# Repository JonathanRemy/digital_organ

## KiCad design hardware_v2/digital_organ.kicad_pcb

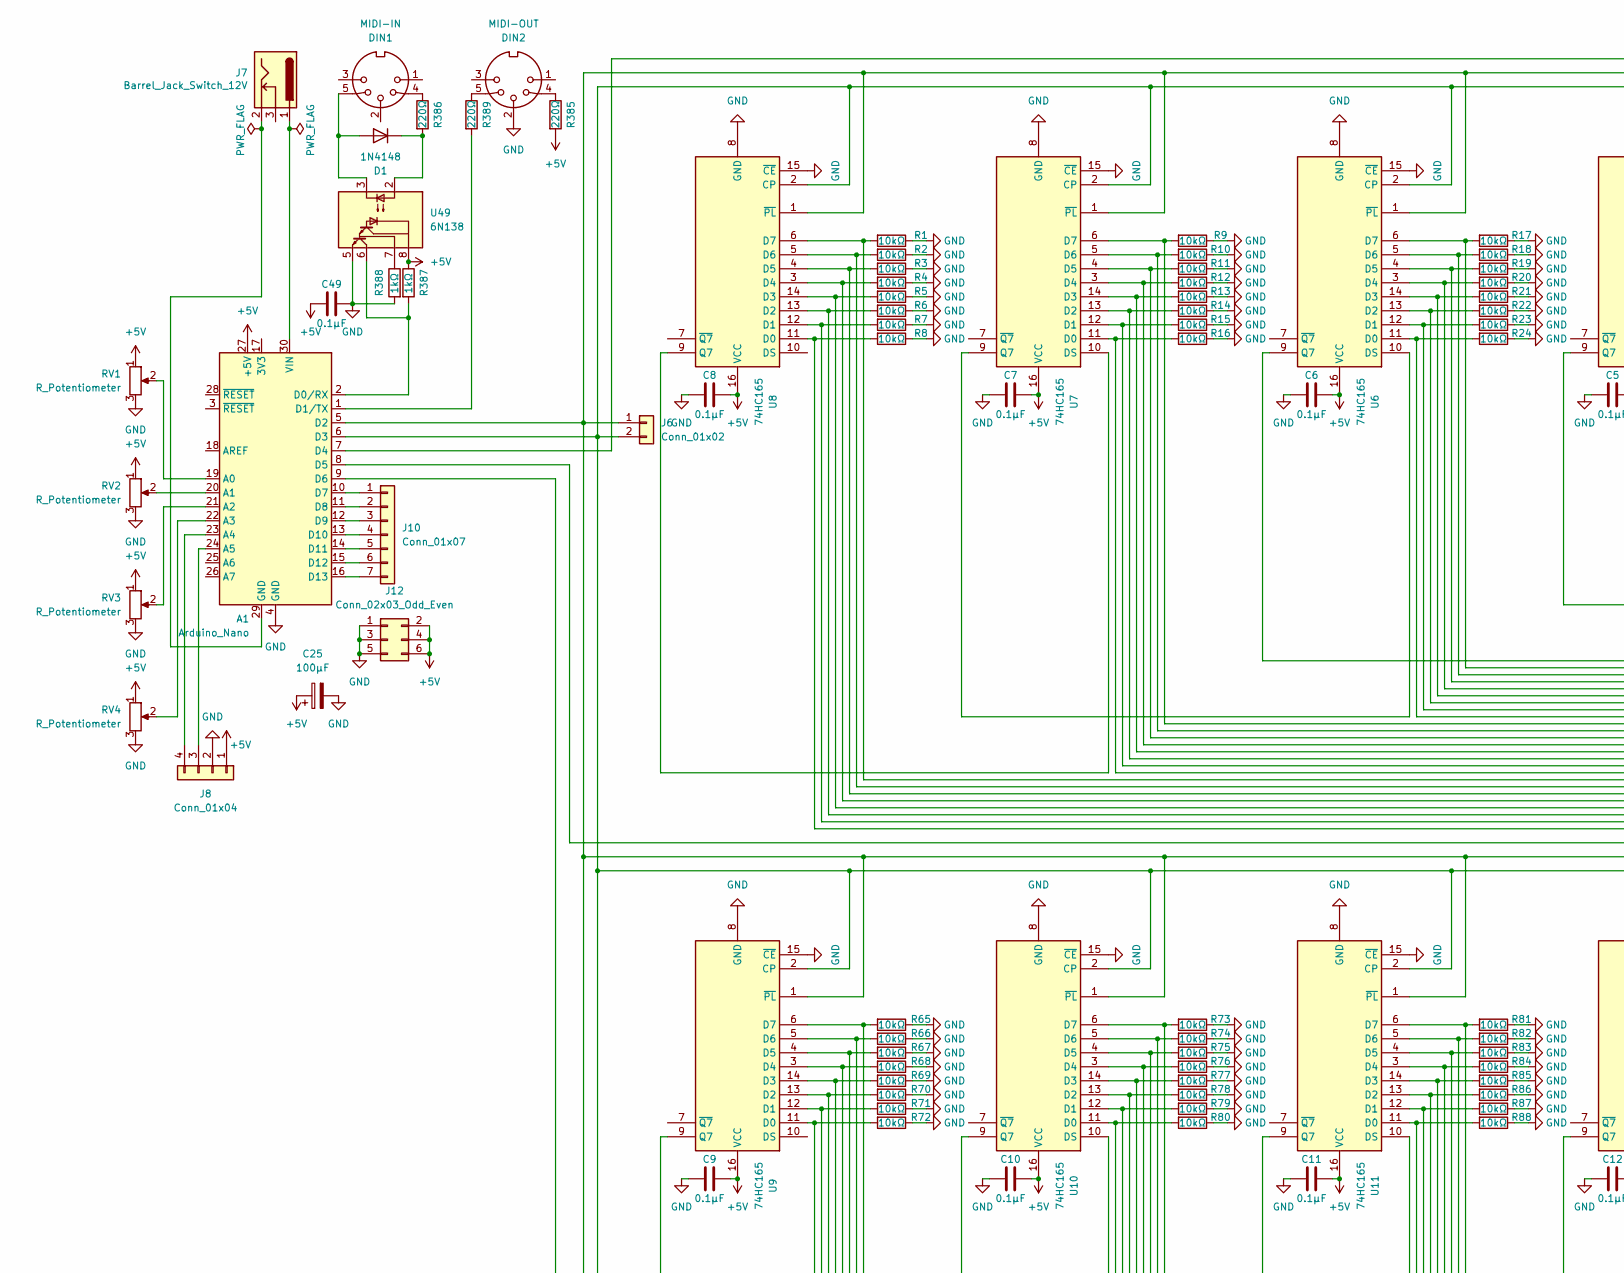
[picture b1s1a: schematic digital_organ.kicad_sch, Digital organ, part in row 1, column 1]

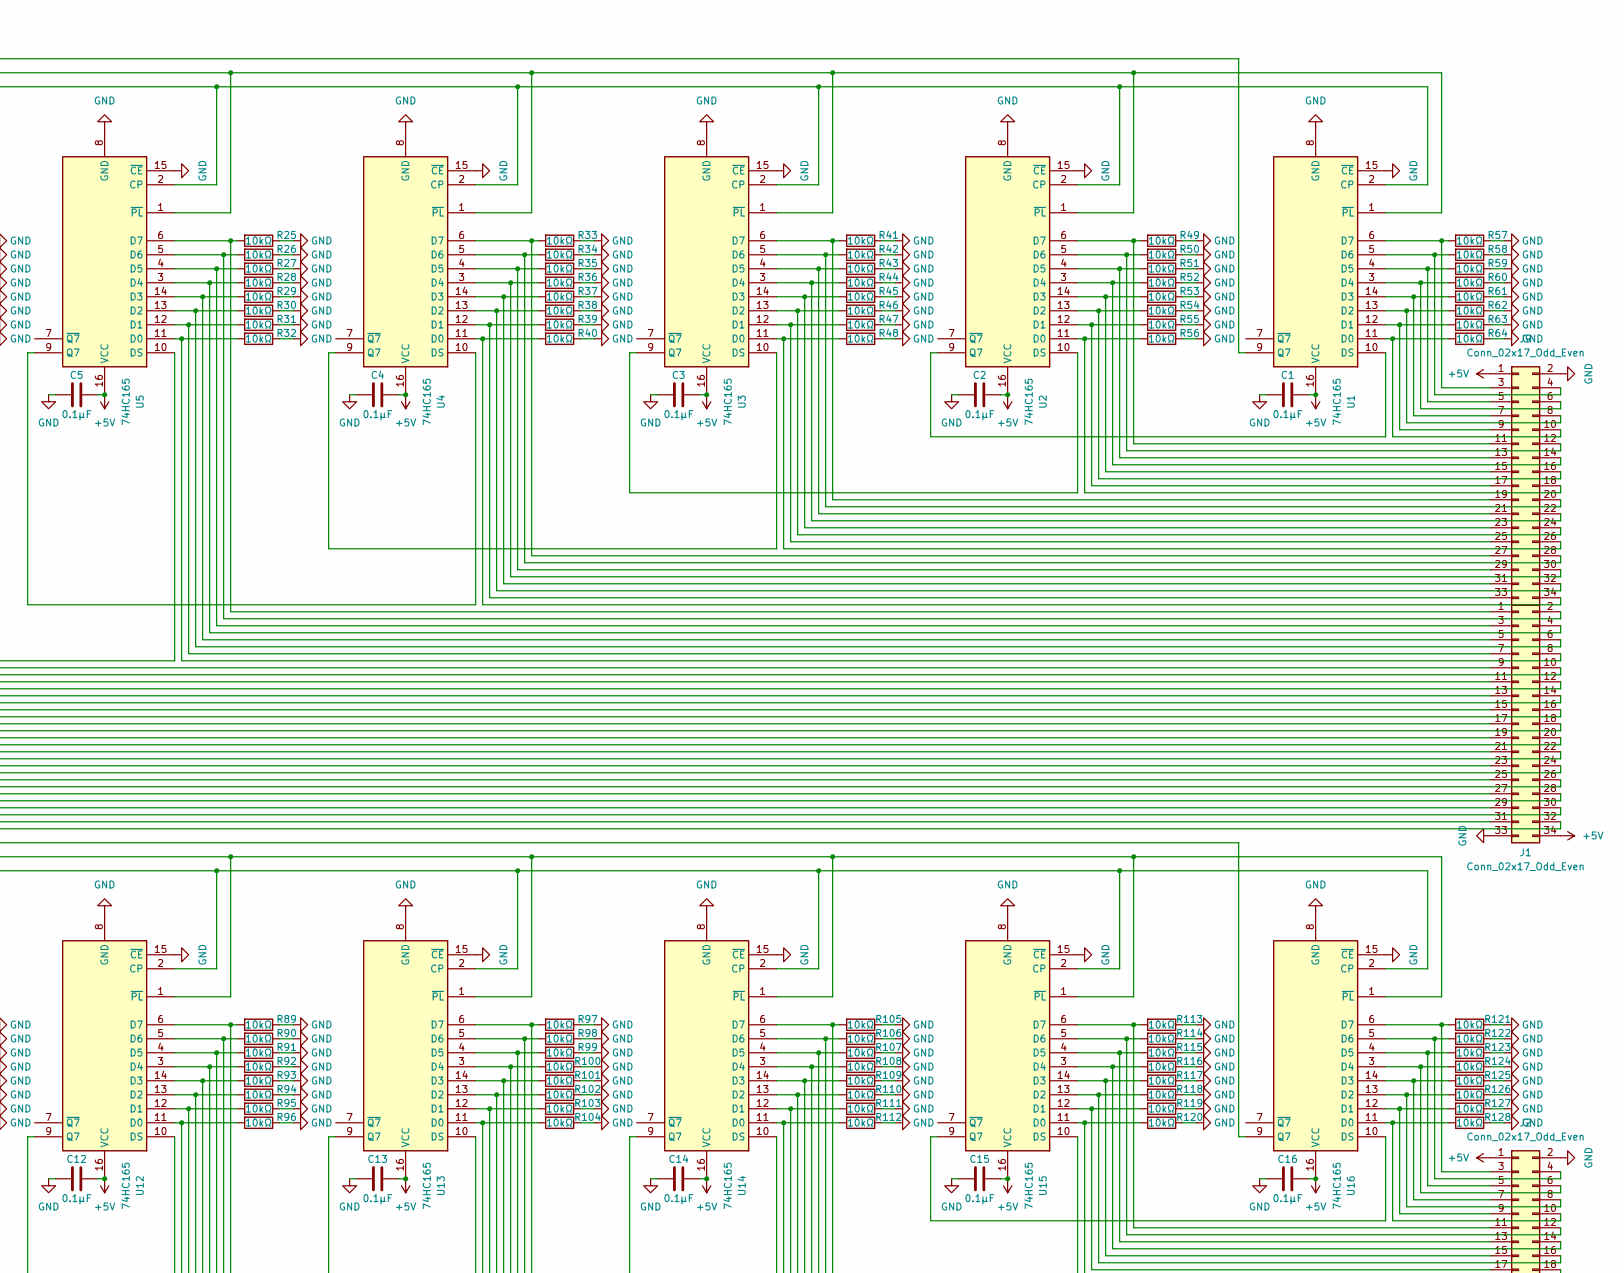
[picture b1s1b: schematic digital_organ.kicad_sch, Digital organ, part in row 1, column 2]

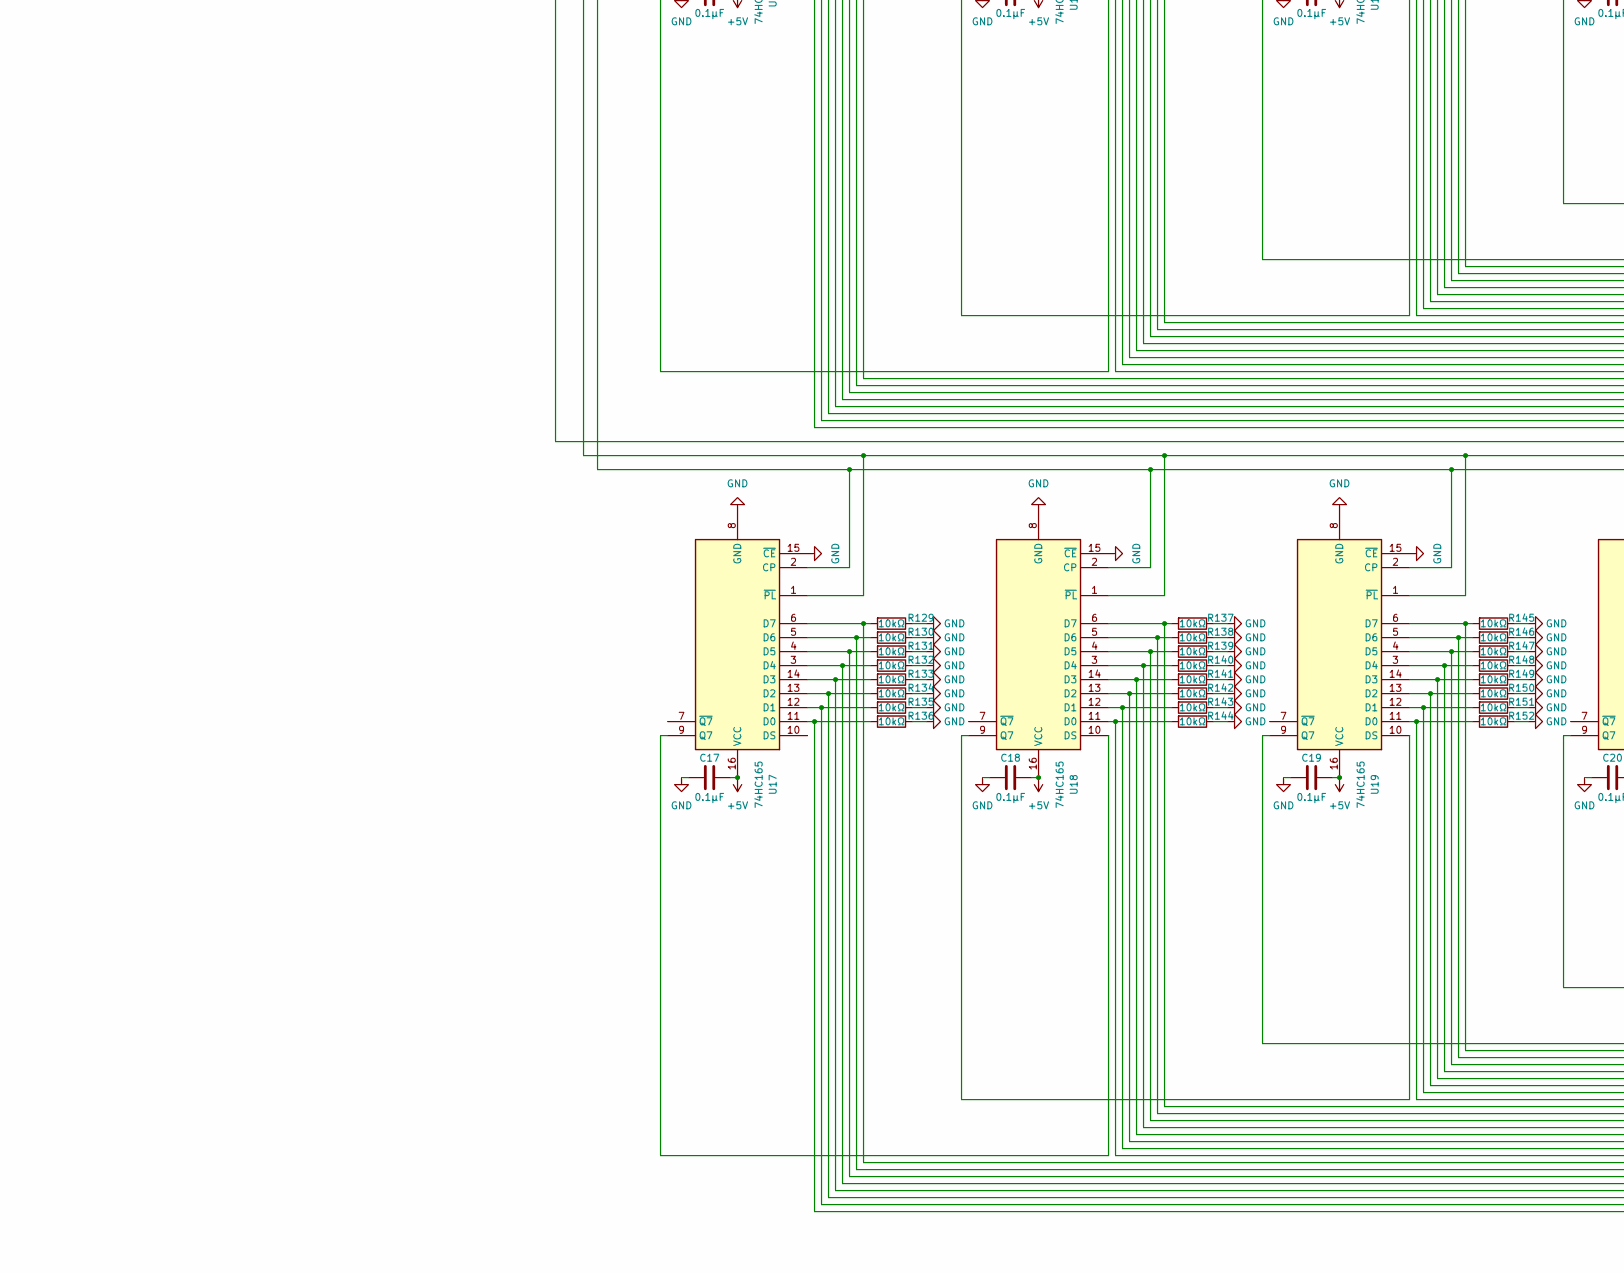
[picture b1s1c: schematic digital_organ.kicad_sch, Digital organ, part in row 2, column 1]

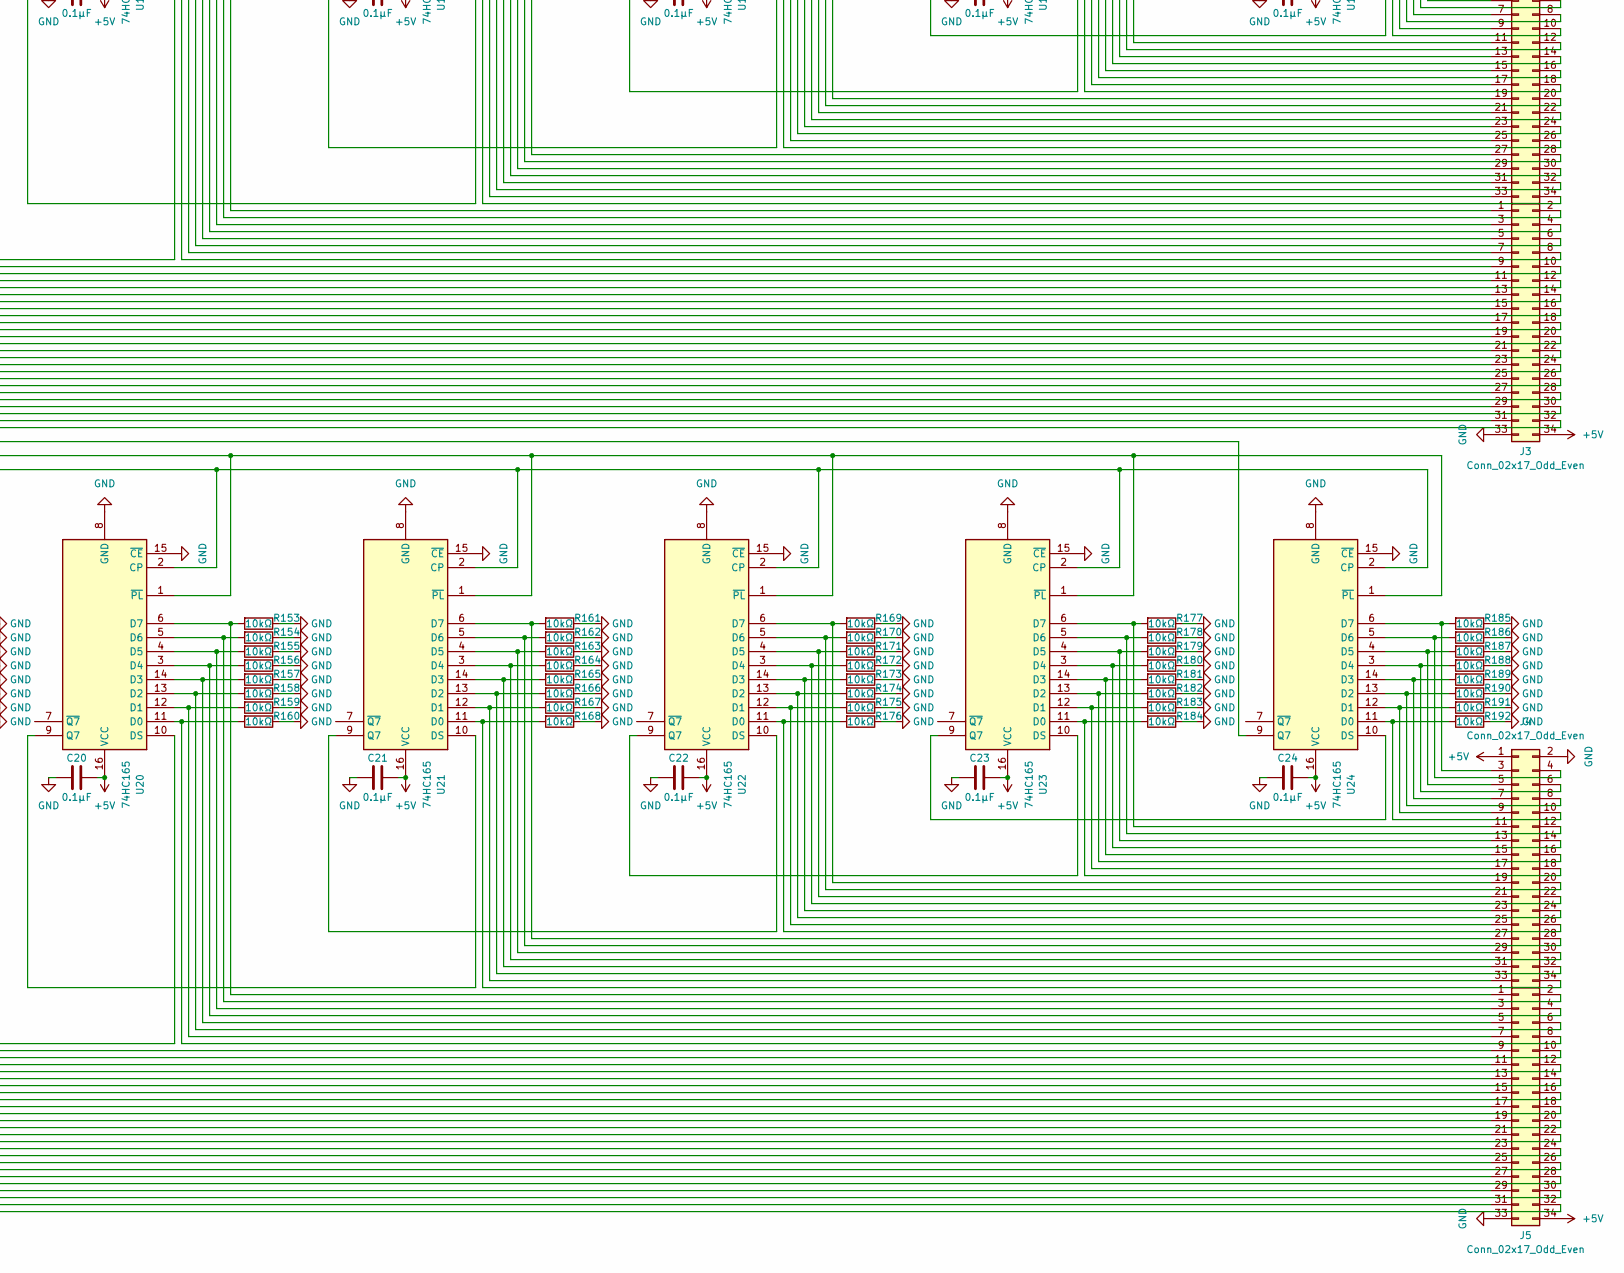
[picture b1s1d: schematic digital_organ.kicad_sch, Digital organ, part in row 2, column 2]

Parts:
A1: Arduino_Nano
C1, C2, C3, C4, C5, C6, C7, C8, C9, C10, C11, C12, C13, C14, C15, C16, C17, C18, C19, C20, C21, C22, C23, C24, C49: 0.1µF; C_Disc_D3.0mm_W1.6mm_P2.50mm
C25: 100µF; CP_Radial_D7.5mm_P2.50mm
D1: 1N4148; D_DO-35_SOD27_P7.62mm_Horizontal
DIN1: MIDI-IN; PinHeader_1x02_P2.54mm_Vertical
DIN2: MIDI-OUT; PinHeader_1x03_P2.54mm_Vertical
J1, J2, J3, J4, J5, J9: Conn_02x17_Odd_Even; IDC-Header_2x17_P2.54mm_Vertical
J6: Conn_01x02; PinHeader_1x02_P2.54mm_Vertical
J7: Barrel_Jack_Switch_12V; PinHeader_1x02_P2.54mm_Vertical
J8: Conn_01x04; PinHeader_1x04_P2.54mm_Vertical
J10: Conn_01x07; PinHeader_1x07_P2.54mm_Vertical
J12: Conn_02x03_Odd_Even; PinHeader_2x03_P2.54mm_Vertical
R1, R2, R3, R4, R5, R6, R7, R8, R9, R10, R11, R12, R13, R14, R15, R16, R17, R18, R19, R20, R21, R22, R23, R24, R25, R26, R27, R28, R29, R30, R31, R32, R33, R34, R35, R36, R37, R38, R39, R40, R41, R42, R43, R44, R45, R46, R47, R48, R49, R50, R51, R52, R53, R54, R55, R56, R57, R58, R59, R60, R61, R62, R63, R64, R65, R66, R67, R68, R69, R70, R71, R72, R73, R74, R75, R76, R77, R78, R79, R80, R81, R82, R83, R84, R85, R86, R87, R88, R89, R90, R91, R92, R93, R94, R95, R96, R97, R98, R99, R100, R101, R102, R103, R104, R105, R106, R107, R108, R109, R110, R111, R112, R113, R114, R115, R116, R117, R118, R119, R120, R121, R122, R123, R124, R125, R126, R127, R128, R129, R130, R131, R132, R133, R134, R135, R136, R137, R138, R139, R140, R141, R142, R143, R144, R145, R146, R147, R148, R149, R150, R151, R152, R153, R154, R155, R156, R157, R158, R159, R160, R161, R162, R163, R164, R165, R166, R167, R168, R169, R170, R171, R172, R173, R174, R175, R176, R177, R178, R179, R180, R181, R182, R183, R184, R185, R186, R187, R188, R189, R190, R191, R192: 10kΩ; R_Axial_DIN0207_L6.3mm_D2.5mm_P10.16mm_Horizontal
R385, R386, R389: 220Ω; R_Axial_DIN0207_L6.3mm_D2.5mm_P10.16mm_Horizontal
R387, R388: 1kΩ; R_Axial_DIN0207_L6.3mm_D2.5mm_P10.16mm_Horizontal
RV1, RV2, RV3, RV4: R_Potentiometer; PinHeader_1x03_P2.54mm_Vertical
U1, U2, U3, U4, U5, U6, U7, U8, U9, U10, U11, U12, U13, U14, U15, U16, U17, U18, U19, U20, U21, U22, U23, U24: 74HC165; DIP-16_W7.62mm_Socket
U49: 6N138; DIP-8_W7.62mm_Socket

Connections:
+5V: A1.27 (+5V), C1.1, C2.1, C3.1, C4.1, C5.1, C6.1, C7.1, C8.1, C9.1, C10.1, C11.1, C12.1, C13.1, C14.1, C15.1, C16.1, C17.1, C18.1, C19.1, C20.1, C21.1, C22.1, C23.1, C24.1, C25.1, C49.2, J1.34, J2.1, J3.34, J4.1, J5.34, J8.1, J9.1, J12.2, J12.4, J12.6, R385.2, R387.1, RV1.1, RV2.1, RV3.1, RV4.1, U1.16 (VCC), U2.16 (VCC), U3.16 (VCC), U4.16 (VCC), U5.16 (VCC), U6.16 (VCC), U7.16 (VCC), U8.16 (VCC), U9.16 (VCC), U10.16 (VCC), U11.16 (VCC), U12.16 (VCC), U13.16 (VCC), U14.16 (VCC), U15.16 (VCC), U16.16 (VCC), U17.16 (VCC), U18.16 (VCC), U19.16 (VCC), U20.16 (VCC), U21.16 (VCC), U22.16 (VCC), U23.16 (VCC), U24.16 (VCC), U49.8 (VCC)
GND: A1.4 (GND), C1.2, C2.2, C3.2, C4.2, C5.2, C6.2, C7.2, C8.2, C9.2, C10.2, C11.2, C12.2, C13.2, C14.2, C15.2, C16.2, C17.2, C18.2, C19.2, C20.2, C21.2, C22.2, C23.2, C24.2, C25.2, C49.1, DIN2.2, J1.33, J2.2, J3.33, J4.2, J5.33, J8.2, J9.2, J12.1, J12.3, J12.5, R1.1, R2.1, R3.1, R4.1, R5.1, R6.1, R7.1, R8.1, R9.1, R10.1, R11.1, R12.1, R13.1, R14.1, R15.1, R16.1, R17.1, R18.1, R19.1, R20.1, R21.1, R22.1, R23.1, R24.1, R25.1, R26.1, R27.1, R28.1, R29.1, R30.1, R31.1, R32.1, R33.1, R34.1, R35.1, R36.1, R37.1, R38.1, R39.1, R40.1, R41.1, R42.1, R43.1, R44.1, R45.1, R46.1, R47.1, R48.1, R49.1, R50.1, R51.1, R52.1, R53.1, R54.1, R55.1, R56.1, R57.1, R58.1, R59.1, R60.1, R61.1, R62.1, R63.1, R64.1, R65.1, R66.1, R67.1, R68.1, R69.1, R70.1, R71.1, R72.1, R73.1, R74.1, R75.1, R76.1, R77.1, R78.1, R79.1, R80.1, R81.1, R82.1, R83.1, R84.1, R85.1, R86.1, R87.1, R88.1, R89.1, R90.1, R91.1, R92.1, R93.1, R94.1, R95.1, R96.1, R97.1, R98.1, R99.1, R100.1, R101.1, R102.1, R103.1, R104.1, R105.1, R106.1, R107.1, R108.1, R109.1, R110.1, R111.1, R112.1, R113.1, R114.1, R115.1, R116.1, R117.1, R118.1, R119.1, R120.1, R121.1, R122.1, R123.1, R124.1, R125.1, R126.1, R127.1, R128.1, R129.1, R130.1, R131.1, R132.1, R133.1, R134.1, R135.1, R136.1, R137.1, R138.1, R139.1, R140.1, R141.1, R142.1, R143.1, R144.1, R145.1, R146.1, R147.1, R148.1, R149.1, R150.1, R151.1, R152.1, R153.1, R154.1, R155.1, R156.1, R157.1, R158.1, R159.1, R160.1, R161.1, R162.1, R163.1, R164.1, R165.1, R166.1, R167.1, R168.1, R169.1, R170.1, R171.1, R172.1, R173.1, R174.1, R175.1, R176.1, R177.1, R178.1, R179.1, R180.1, R181.1, R182.1, R183.1, R184.1, R185.1, R186.1, R187.1, R188.1, R189.1, R190.1, R191.1, R192.1, R388.2, RV1.3, RV2.3, RV3.3, RV4.3, U1.8 (GND), U1.15 (~CE), U2.8 (GND), U2.15 (~CE), U3.8 (GND), U3.15 (~CE), U4.8 (GND), U4.15 (~CE), U5.8 (GND), U5.15 (~CE), U6.8 (GND), U6.15 (~CE), U7.8 (GND), U7.15 (~CE), U8.8 (GND), U8.15 (~CE), U9.8 (GND), U9.15 (~CE), U10.8 (GND), U10.15 (~CE), U11.8 (GND), U11.15 (~CE), U12.8 (GND), U12.15 (~CE), U13.8 (GND), U13.15 (~CE), U14.8 (GND), U14.15 (~CE), U15.8 (GND), U15.15 (~CE), U16.8 (GND), U16.15 (~CE), U17.8 (GND), U17.15 (~CE), U18.8 (GND), U18.15 (~CE), U19.8 (GND), U19.15 (~CE), U20.8 (GND), U20.15 (~CE), U21.8 (GND), U21.15 (~CE), U22.8 (GND), U22.15 (~CE), U23.8 (GND), U23.15 (~CE), U24.8 (GND), U24.15 (~CE), U49.5 (GND)
unnamed: A1.19 (A0), RV1.2
unnamed: A1.20 (A1), RV2.2
unnamed: A1.21 (A2), RV3.2
unnamed: A1.22 (A3), RV4.2
unnamed: A1.23 (A4), J8.4
unnamed: A1.24 (A5), J8.3
unnamed: A1.2 (D0/RX), R387.2, U49.6 (VO2)
unnamed: A1.1 (D1/TX), R389.2
unnamed: A1.5 (D2), J6.1, U1.1 (~PL), U2.1 (~PL), U3.1 (~PL), U4.1 (~PL), U5.1 (~PL), U6.1 (~PL), U7.1 (~PL), U8.1 (~PL), U9.1 (~PL), U10.1 (~PL), U11.1 (~PL), U12.1 (~PL), U13.1 (~PL), U14.1 (~PL), U15.1 (~PL), U16.1 (~PL), U17.1 (~PL), U18.1 (~PL), U19.1 (~PL), U20.1 (~PL), U21.1 (~PL), U22.1 (~PL), U23.1 (~PL), U24.1 (~PL)
unnamed: A1.6 (D3), J6.2, U1.2 (CP), U2.2 (CP), U3.2 (CP), U4.2 (CP), U5.2 (CP), U6.2 (CP), U7.2 (CP), U8.2 (CP), U9.2 (CP), U10.2 (CP), U11.2 (CP), U12.2 (CP), U13.2 (CP), U14.2 (CP), U15.2 (CP), U16.2 (CP), U17.2 (CP), U18.2 (CP), U19.2 (CP), U20.2 (CP), U21.2 (CP), U22.2 (CP), U23.2 (CP), U24.2 (CP)
unnamed: A1.7 (D4), U1.9 (Q7)
unnamed: A1.8 (D5), U16.9 (Q7)
unnamed: A1.9 (D6), U24.9 (Q7)
unnamed: A1.10 (D7), J10.1
unnamed: A1.11 (D8), J10.2
unnamed: A1.12 (D9), J10.3
unnamed: A1.13 (D10), J10.4
unnamed: A1.14 (D11), J10.5
unnamed: A1.15 (D12), J10.6
unnamed: A1.16 (D13), J10.7
unnamed: A1.29 (GND), J7.2
unnamed: A1.30 (VIN), J7.1
unnamed: D1.2 (A), DIN1.5, U49.3 (C2)
unnamed: D1.1 (K), R386.2, U49.2 (C1)
unnamed: DIN1.4, R386.1
unnamed: DIN2.4, R385.1
unnamed: DIN2.5, R389.1
unnamed: J1.1, R25.2, U5.6 (D7)
unnamed: J1.2, R26.2, U5.5 (D6)
unnamed: J1.3, R27.2, U5.4 (D5)
unnamed: J1.4, R28.2, U5.3 (D4)
unnamed: J1.5, R29.2, U5.14 (D3)
unnamed: J1.6, R30.2, U5.13 (D2)
unnamed: J1.7, R31.2, U5.12 (D1)
unnamed: J1.8, R32.2, U5.11 (D0)
unnamed: J1.9, R17.2, U6.6 (D7)
unnamed: J1.10, R18.2, U6.5 (D6)
unnamed: J1.11, R19.2, U6.4 (D5)
unnamed: J1.12, R20.2, U6.3 (D4)
unnamed: J1.13, R21.2, U6.14 (D3)
unnamed: J1.14, R22.2, U6.13 (D2)
unnamed: J1.15, R23.2, U6.12 (D1)
unnamed: J1.16, R24.2, U6.11 (D0)
unnamed: J1.17, R9.2, U7.6 (D7)
unnamed: J1.18, R10.2, U7.5 (D6)
unnamed: J1.19, R11.2, U7.4 (D5)
unnamed: J1.20, R12.2, U7.3 (D4)
unnamed: J1.21, R13.2, U7.14 (D3)
unnamed: J1.22, R14.2, U7.13 (D2)
unnamed: J1.23, R15.2, U7.12 (D1)
unnamed: J1.24, R16.2, U7.11 (D0)
unnamed: J1.25, R1.2, U8.6 (D7)
unnamed: J1.26, R2.2, U8.5 (D6)
unnamed: J1.27, R3.2, U8.4 (D5)
unnamed: J1.28, R4.2, U8.3 (D4)
unnamed: J1.29, R5.2, U8.14 (D3)
unnamed: J1.30, R6.2, U8.13 (D2)
unnamed: J1.31, R7.2, U8.12 (D1)
unnamed: J1.32, R8.2, U8.11 (D0)
unnamed: J2.3, R121.2, U16.6 (D7)
unnamed: J2.4, R122.2, U16.5 (D6)
unnamed: J2.5, R123.2, U16.4 (D5)
unnamed: J2.6, R124.2, U16.3 (D4)
unnamed: J2.7, R125.2, U16.14 (D3)
unnamed: J2.8, R126.2, U16.13 (D2)
unnamed: J2.9, R127.2, U16.12 (D1)
unnamed: J2.10, R128.2, U16.11 (D0)
unnamed: J2.11, R113.2, U15.6 (D7)
unnamed: J2.12, R114.2, U15.5 (D6)
unnamed: J2.13, R115.2, U15.4 (D5)
unnamed: J2.14, R116.2, U15.3 (D4)
unnamed: J2.15, R117.2, U15.14 (D3)
unnamed: J2.16, R118.2, U15.13 (D2)
unnamed: J2.17, R119.2, U15.12 (D1)
unnamed: J2.18, R120.2, U15.11 (D0)
unnamed: J2.19, R105.2, U14.6 (D7)
unnamed: J2.20, R106.2, U14.5 (D6)
unnamed: J2.21, R107.2, U14.4 (D5)
unnamed: J2.22, R108.2, U14.3 (D4)
unnamed: J2.23, R109.2, U14.14 (D3)
unnamed: J2.24, R110.2, U14.13 (D2)
unnamed: J2.25, R111.2, U14.12 (D1)
unnamed: J2.26, R112.2, U14.11 (D0)
unnamed: J2.27, R97.2, U13.6 (D7)
unnamed: J2.28, R98.2, U13.5 (D6)
unnamed: J2.29, R99.2, U13.4 (D5)
unnamed: J2.30, R100.2, U13.3 (D4)
unnamed: J2.31, R101.2, U13.14 (D3)
unnamed: J2.32, R102.2, U13.13 (D2)
unnamed: J2.33, R103.2, U13.12 (D1)
unnamed: J2.34, R104.2, U13.11 (D0)
unnamed: J3.1, R89.2, U12.6 (D7)
unnamed: J3.2, R90.2, U12.5 (D6)
unnamed: J3.3, R91.2, U12.4 (D5)
unnamed: J3.4, R92.2, U12.3 (D4)
unnamed: J3.5, R93.2, U12.14 (D3)
unnamed: J3.6, R94.2, U12.13 (D2)
unnamed: J3.7, R95.2, U12.12 (D1)
unnamed: J3.8, R96.2, U12.11 (D0)
unnamed: J3.9, R81.2, U11.6 (D7)
unnamed: J3.10, R82.2, U11.5 (D6)
unnamed: J3.11, R83.2, U11.4 (D5)
unnamed: J3.12, R84.2, U11.3 (D4)
unnamed: J3.13, R85.2, U11.14 (D3)
unnamed: J3.14, R86.2, U11.13 (D2)
unnamed: J3.15, R87.2, U11.12 (D1)
unnamed: J3.16, R88.2, U11.11 (D0)
unnamed: J3.17, R73.2, U10.6 (D7)
unnamed: J3.18, R74.2, U10.5 (D6)
unnamed: J3.19, R75.2, U10.4 (D5)
unnamed: J3.20, R76.2, U10.3 (D4)
unnamed: J3.21, R77.2, U10.14 (D3)
unnamed: J3.22, R78.2, U10.13 (D2)
unnamed: J3.23, R79.2, U10.12 (D1)
unnamed: J3.24, R80.2, U10.11 (D0)
unnamed: J3.25, R65.2, U9.6 (D7)
unnamed: J3.26, R66.2, U9.5 (D6)
unnamed: J3.27, R67.2, U9.4 (D5)
unnamed: J3.28, R68.2, U9.3 (D4)
unnamed: J3.29, R69.2, U9.14 (D3)
unnamed: J3.30, R70.2, U9.13 (D2)
unnamed: J3.31, R71.2, U9.12 (D1)
unnamed: J3.32, R72.2, U9.11 (D0)
unnamed: J4.3, R185.2, U24.6 (D7)
unnamed: J4.4, R186.2, U24.5 (D6)
unnamed: J4.5, R187.2, U24.4 (D5)
unnamed: J4.6, R188.2, U24.3 (D4)
unnamed: J4.7, R189.2, U24.14 (D3)
unnamed: J4.8, R190.2, U24.13 (D2)
unnamed: J4.9, R191.2, U24.12 (D1)
unnamed: J4.10, R192.2, U24.11 (D0)
unnamed: J4.11, R177.2, U23.6 (D7)
unnamed: J4.12, R178.2, U23.5 (D6)
unnamed: J4.13, R179.2, U23.4 (D5)
unnamed: J4.14, R180.2, U23.3 (D4)
unnamed: J4.15, R181.2, U23.14 (D3)
unnamed: J4.16, R182.2, U23.13 (D2)
unnamed: J4.17, R183.2, U23.12 (D1)
unnamed: J4.18, R184.2, U23.11 (D0)
unnamed: J4.19, R169.2, U22.6 (D7)
unnamed: J4.20, R170.2, U22.5 (D6)
unnamed: J4.21, R171.2, U22.4 (D5)
unnamed: J4.22, R172.2, U22.3 (D4)
unnamed: J4.23, R173.2, U22.14 (D3)
unnamed: J4.24, R174.2, U22.13 (D2)
unnamed: J4.25, R175.2, U22.12 (D1)
unnamed: J4.26, R176.2, U22.11 (D0)
unnamed: J4.27, R161.2, U21.6 (D7)
unnamed: J4.28, R162.2, U21.5 (D6)
unnamed: J4.29, R163.2, U21.4 (D5)
unnamed: J4.30, R164.2, U21.3 (D4)
unnamed: J4.31, R165.2, U21.14 (D3)
unnamed: J4.32, R166.2, U21.13 (D2)
unnamed: J4.33, R167.2, U21.12 (D1)
unnamed: J4.34, R168.2, U21.11 (D0)
unnamed: J5.1, R153.2, U20.6 (D7)
unnamed: J5.2, R154.2, U20.5 (D6)
unnamed: J5.3, R155.2, U20.4 (D5)
unnamed: J5.4, R156.2, U20.3 (D4)
unnamed: J5.5, R157.2, U20.14 (D3)
unnamed: J5.6, R158.2, U20.13 (D2)
unnamed: J5.7, R159.2, U20.12 (D1)
unnamed: J5.8, R160.2, U20.11 (D0)
unnamed: J5.9, R145.2, U19.6 (D7)
unnamed: J5.10, R146.2, U19.5 (D6)
unnamed: J5.11, R147.2, U19.4 (D5)
unnamed: J5.12, R148.2, U19.3 (D4)
unnamed: J5.13, R149.2, U19.14 (D3)
unnamed: J5.14, R150.2, U19.13 (D2)
unnamed: J5.15, R151.2, U19.12 (D1)
unnamed: J5.16, R152.2, U19.11 (D0)
unnamed: J5.17, R137.2, U18.6 (D7)
unnamed: J5.18, R138.2, U18.5 (D6)
unnamed: J5.19, R139.2, U18.4 (D5)
unnamed: J5.20, R140.2, U18.3 (D4)
unnamed: J5.21, R141.2, U18.14 (D3)
unnamed: J5.22, R142.2, U18.13 (D2)
unnamed: J5.23, R143.2, U18.12 (D1)
unnamed: J5.24, R144.2, U18.11 (D0)
unnamed: J5.25, R129.2, U17.6 (D7)
unnamed: J5.26, R130.2, U17.5 (D6)
unnamed: J5.27, R131.2, U17.4 (D5)
unnamed: J5.28, R132.2, U17.3 (D4)
unnamed: J5.29, R133.2, U17.14 (D3)
unnamed: J5.30, R134.2, U17.13 (D2)
unnamed: J5.31, R135.2, U17.12 (D1)
unnamed: J5.32, R136.2, U17.11 (D0)
unnamed: J9.3, R57.2, U1.6 (D7)
unnamed: J9.4, R58.2, U1.5 (D6)
unnamed: J9.5, R59.2, U1.4 (D5)
unnamed: J9.6, R60.2, U1.3 (D4)
unnamed: J9.7, R61.2, U1.14 (D3)
unnamed: J9.8, R62.2, U1.13 (D2)
unnamed: J9.9, R63.2, U1.12 (D1)
unnamed: J9.10, R64.2, U1.11 (D0)
unnamed: J9.11, R49.2, U2.6 (D7)
unnamed: J9.12, R50.2, U2.5 (D6)
unnamed: J9.13, R51.2, U2.4 (D5)
unnamed: J9.14, R52.2, U2.3 (D4)
unnamed: J9.15, R53.2, U2.14 (D3)
unnamed: J9.16, R54.2, U2.13 (D2)
unnamed: J9.17, R55.2, U2.12 (D1)
unnamed: J9.18, R56.2, U2.11 (D0)
unnamed: J9.19, R41.2, U3.6 (D7)
unnamed: J9.20, R42.2, U3.5 (D6)
unnamed: J9.21, R43.2, U3.4 (D5)
unnamed: J9.22, R44.2, U3.3 (D4)
unnamed: J9.23, R45.2, U3.14 (D3)
unnamed: J9.24, R46.2, U3.13 (D2)
unnamed: J9.25, R47.2, U3.12 (D1)
unnamed: J9.26, R48.2, U3.11 (D0)
unnamed: J9.27, R33.2, U4.6 (D7)
unnamed: J9.28, R34.2, U4.5 (D6)
unnamed: J9.29, R35.2, U4.4 (D5)
unnamed: J9.30, R36.2, U4.3 (D4)
unnamed: J9.31, R37.2, U4.14 (D3)
unnamed: J9.32, R38.2, U4.13 (D2)
unnamed: J9.33, R39.2, U4.12 (D1)
unnamed: J9.34, R40.2, U4.11 (D0)
unnamed: U1.10 (DS), U2.9 (Q7)
unnamed: U2.10 (DS), U3.9 (Q7)
unnamed: U3.10 (DS), U4.9 (Q7)
unnamed: U4.10 (DS), U5.9 (Q7)
unnamed: U5.10 (DS), U6.9 (Q7)
unnamed: U6.10 (DS), U7.9 (Q7)
unnamed: U7.10 (DS), U8.9 (Q7)
unnamed: U9.9 (Q7), U10.10 (DS)
unnamed: U10.9 (Q7), U11.10 (DS)
unnamed: U11.9 (Q7), U12.10 (DS)
unnamed: U12.9 (Q7), U13.10 (DS)
unnamed: U13.9 (Q7), U14.10 (DS)
unnamed: U14.9 (Q7), U15.10 (DS)
unnamed: U15.9 (Q7), U16.10 (DS)
unnamed: U17.9 (Q7), U18.10 (DS)
unnamed: U18.9 (Q7), U19.10 (DS)
unnamed: U19.9 (Q7), U20.10 (DS)
unnamed: U20.9 (Q7), U21.10 (DS)
unnamed: U21.9 (Q7), U22.10 (DS)
unnamed: U22.9 (Q7), U23.10 (DS)
unnamed: U23.9 (Q7), U24.10 (DS)
unnamed: R388.1, U49.7 (VO1)

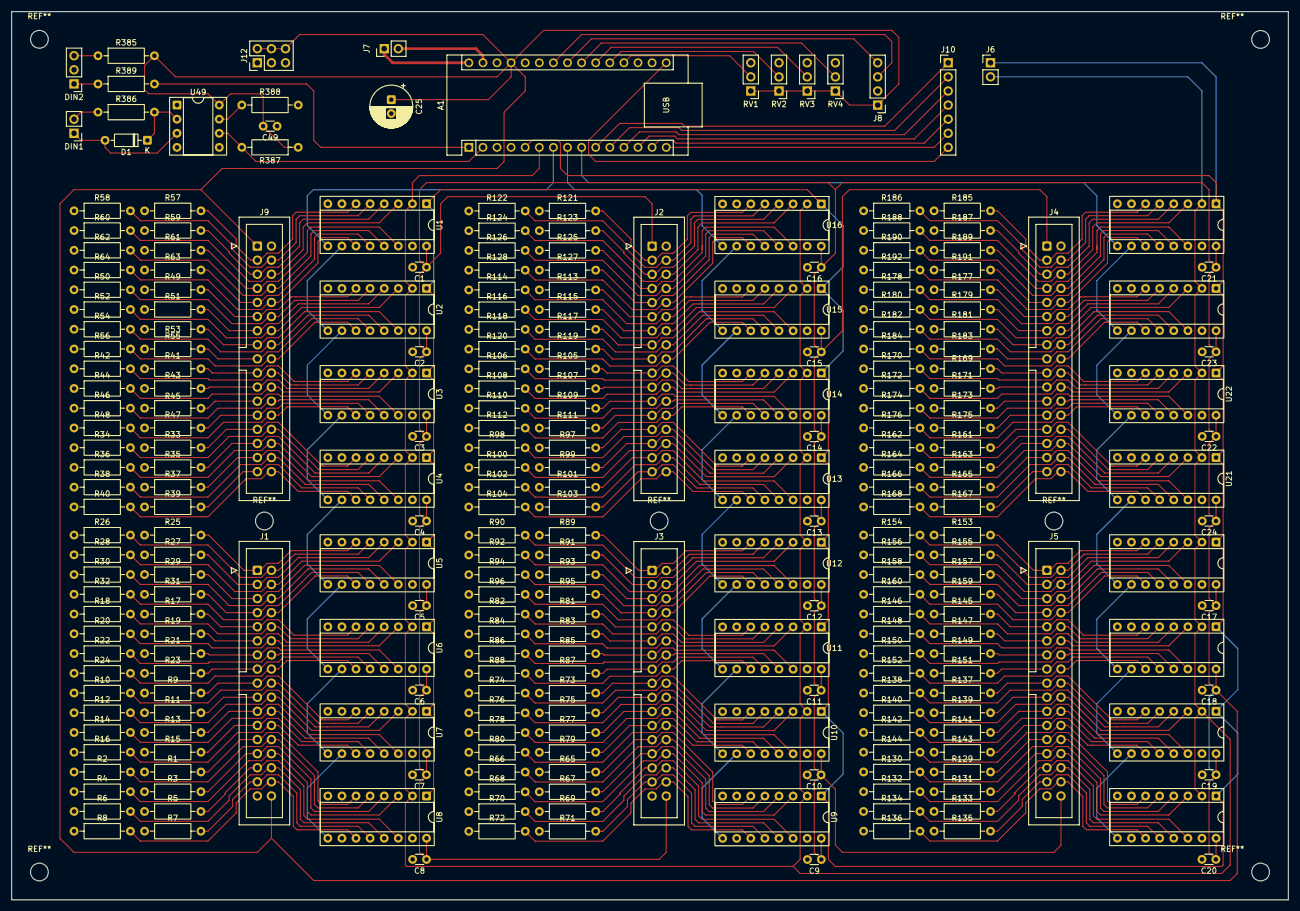
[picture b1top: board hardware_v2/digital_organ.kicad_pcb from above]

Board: 2 copper layers, 230.0 x 160.0 mm, 267 parts (0 on the bottom side), 243 nets.

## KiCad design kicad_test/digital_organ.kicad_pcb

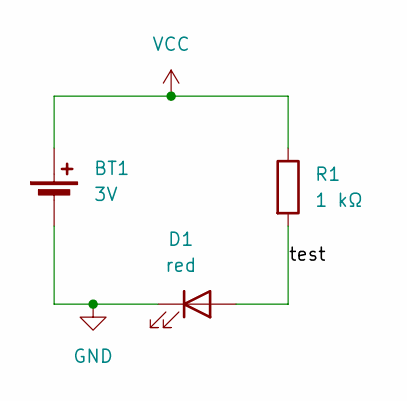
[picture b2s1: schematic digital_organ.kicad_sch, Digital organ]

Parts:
BT1: 3V; BatteryHolder_Keystone_1058_1x2032
D1: red; LED_D5.0mm
R1: 1 kΩ; R_Axial_DIN0309_L9.0mm_D3.2mm_P12.70mm_Horizontal

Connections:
/test: D1.2 (A), R1.2
GND: BT1.2 (-), D1.1 (K)
VCC: BT1.1 (+), R1.1

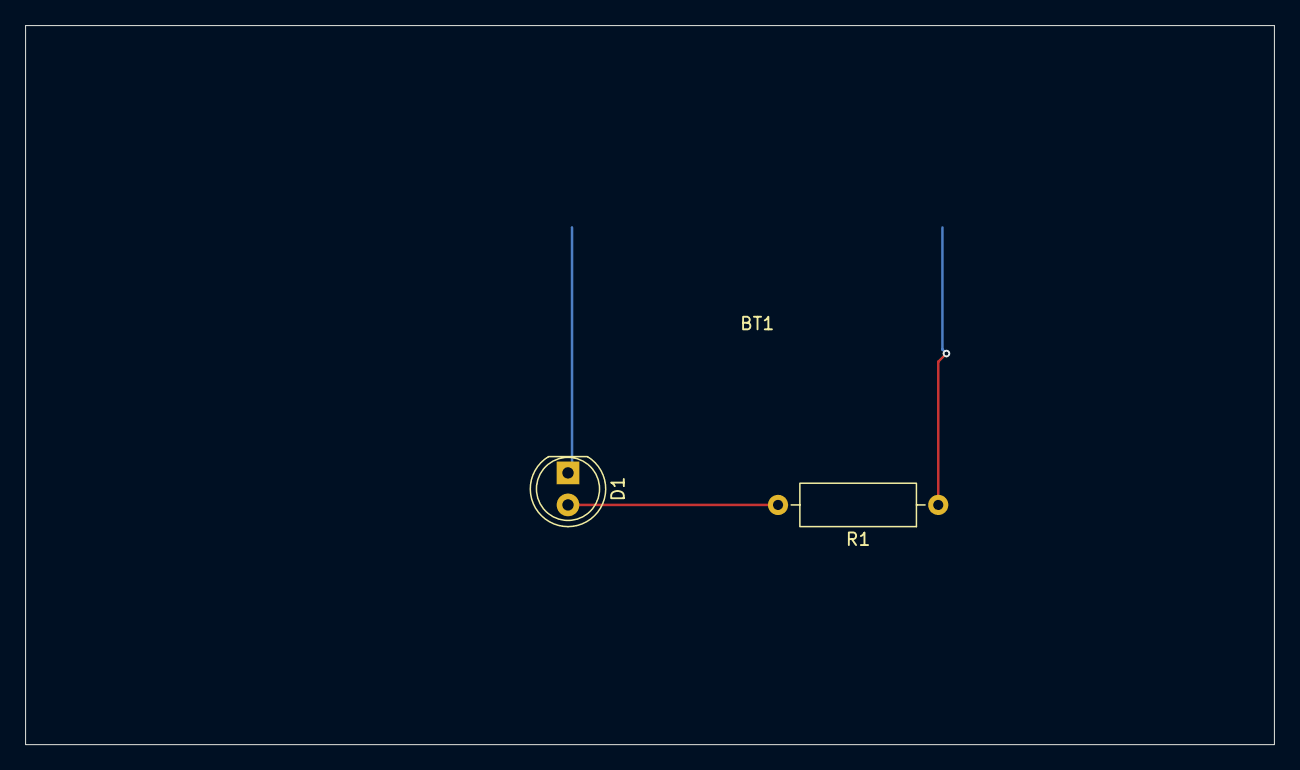
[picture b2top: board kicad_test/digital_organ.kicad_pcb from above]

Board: 2 copper layers, 99.0 x 57.0 mm, 3 parts (1 on the bottom side), 3 nets.

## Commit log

2025-09-02 Getting starting with KiCad
2025-09-04 Begin schematic
2025-09-11 Update schematic
2025-09-29 Update pcb
2025-11-25 Update software
